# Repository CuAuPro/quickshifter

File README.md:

# Quickshifter
Quickshifter for motorcycle.

<!-- ABOUT THE PROJECT -->
## About The Project

Quickshifter for motorcycles based on measured force on gearbox. Implemented is pull-type quicksihfter but it allows, with small modifications, push-type also.

<p align="right">(<a href="#top">back to top</a>)</p>

### Built With

* [KiCad](https://www.kicad.org/)
* [STM32CubeIDE](https://www.st.com/en/development-tools/stm32cubeide.html)

<p align="right">(<a href="#top">back to top</a>)</p>

### Contents

* PCB
* Firmware

<p align="right">(<a href="#top">back to top</a>)</p>

<!-- CONTACT -->
## Contact

Kristjan Cuznar - [LinkedIn](https://www.linkedin.com/in/kristjan-cuznar/) - kristjancuznar0@gmail.com

Project Link: [https://github.com/CuAuPro/quickshifter)

<p align="right">(<a href="#top">back to top</a>)</p>

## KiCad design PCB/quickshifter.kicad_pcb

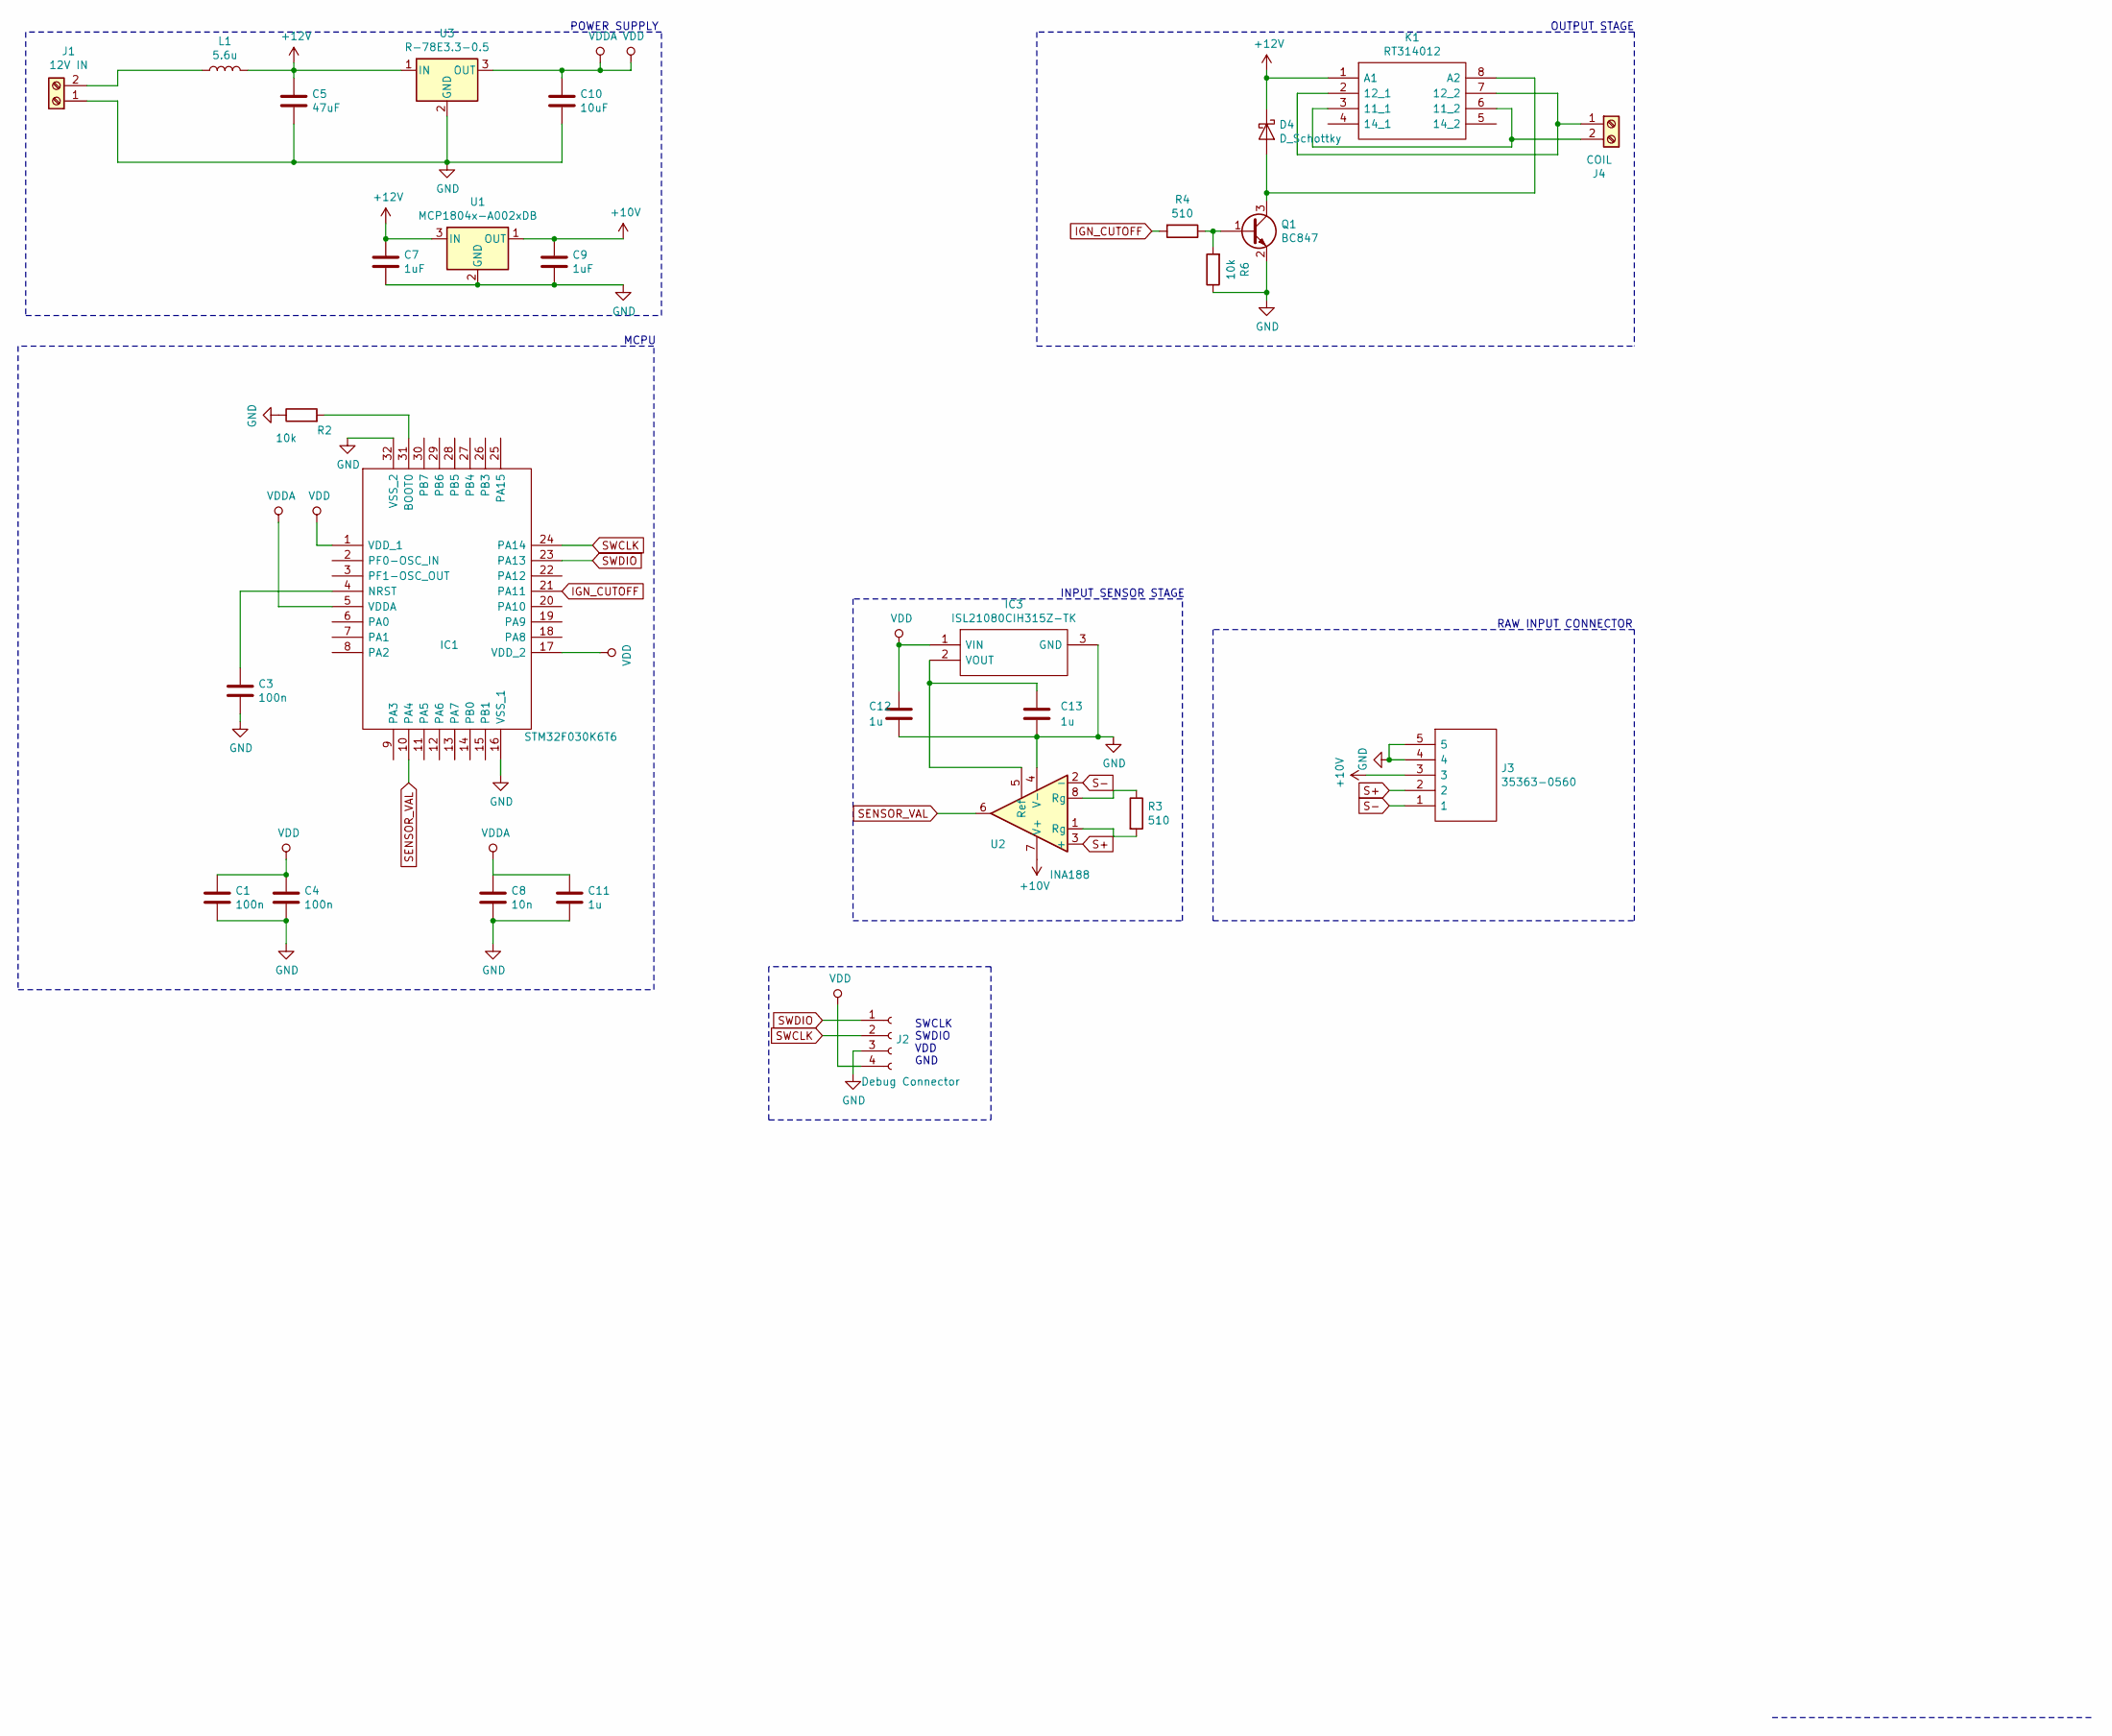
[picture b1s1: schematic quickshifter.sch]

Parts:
C1, C3, C4: 100n; C_0805_2012Metric_Pad1.18x1.45mm_HandSolder
C5: 47uF; C_0805_2012Metric_Pad1.18x1.45mm_HandSolder
C7, C9: 1uF; C_0805_2012Metric_Pad1.18x1.45mm_HandSolder
C8: 10n; C_0805_2012Metric_Pad1.18x1.45mm_HandSolder
C10: 10uF; C_0805_2012Metric_Pad1.18x1.45mm_HandSolder
C11, C12, C13: 1u; C_0805_2012Metric_Pad1.18x1.45mm_HandSolder
D4: D_Schottky; D_SOD-123; Farnell 2473410
IC1: STM32F030K6T6; QFP80P900X900X120-32N; Farnell 2432085
IC3: ISL21080CIH315Z-TK; SOT95P237X112-3N; Farnell 2358142
J1: 12V IN; SHDR2W80P0X350_1X2_840X920X720P
J2: Debug Connector; PinHeader_1x04_P2.54mm_Vertical
J3: 35363-0560; 353630560; Farnell 3107233
J4: COIL; SHDR2W80P0X350_1X2_840X920X720P
K1: RT314012; RT314005_2; Farnell 1629044
L1: 5.6u; L_0805_2012Metric_Pad1.15x1.40mm_HandSolder
Q1: BC847; SOT-23
R2, R6: 10k; R_0805_2012Metric_Pad1.20x1.40mm_HandSolder
R3, R4: 510; R_0805_2012Metric_Pad1.20x1.40mm_HandSolder
U1: MCP1804x-A002xDB; SOT-223-3_TabPin2
U2: INA188; SOIC-8_3.9x4.9mm_P1.27mm
U3: R-78E3.3-0.5; Converter_DCDC_RECOM_R-78E-0.5_THT

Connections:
+10V: C9.1, J3.3, U1.1 (OUT), U2.7 (V+)
+12V: C5.1, C7.1, D4.1 (K), K1.1 (A1), L1.2, U1.3 (IN), U3.1 (IN)
GND: C1.2, C3.2, C4.2, C5.2, C7.2, C8.2, C9.2, C10.2, C11.2, C12.2, C13.2, IC1.16 (VSS_1), IC1.32 (VSS_2), IC3.3 (GND), J1.1, J2.3, J3.4, J3.5, Q1.2 (E), R2.1, R6.1, U1.2 (GND), U2.4 (V-), U3.2 (GND)
IGN_CUTOFF: IC1.21 (PA11), R4.2
unnamed: C3.1, IC1.4 (NRST)
unnamed: C13.1, IC3.2 (VOUT), U2.5 (Ref)
unnamed: D4.2 (A), K1.8 (A2), Q1.3 (C)
unnamed: IC1.31 (BOOT0), R2.2
unnamed: J1.2, L1.1
unnamed: J4.1, K1.2 (12_1), K1.7 (12_2)
unnamed: J4.2, K1.3 (11_1), K1.6 (11_2)
unnamed: Q1.1 (B), R4.1, R6.2
unnamed: R3.1, U2.8 (Rg)
unnamed: R3.2, U2.1 (Rg)
S+: J3.2, U2.3 (+)
S-: J3.1, U2.2 (-)
SENSOR_VAL: IC1.10 (PA4), U2.6
SWCLK: IC1.24 (PA14), J2.2
SWDIO: IC1.23 (PA13), J2.1
VDD: C1.1, C4.1, C8.1, C10.1, C11.1, C12.1, IC1.1 (VDD_1), IC1.5 (VDDA), IC1.17 (VDD_2), IC3.1 (VIN), J2.4, U3.3 (OUT)

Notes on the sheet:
POWER SUPPLY
MCPU
SWCLK SWDIO VDD GND
RAW INPUT CONNECTOR
INPUT SENSOR STAGE
OUTPUT STAGE

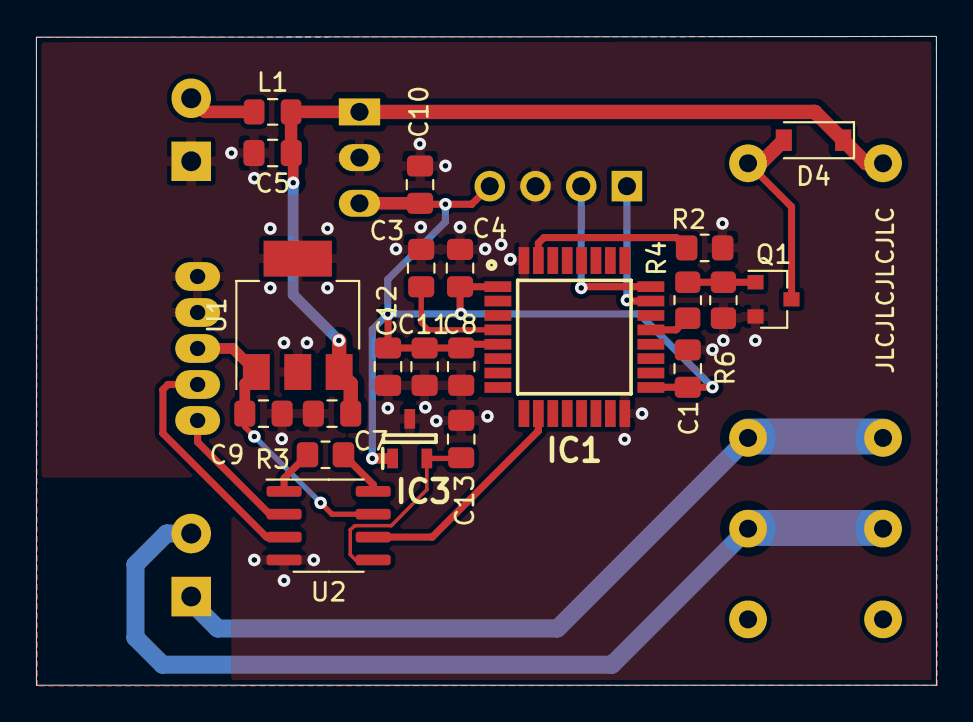
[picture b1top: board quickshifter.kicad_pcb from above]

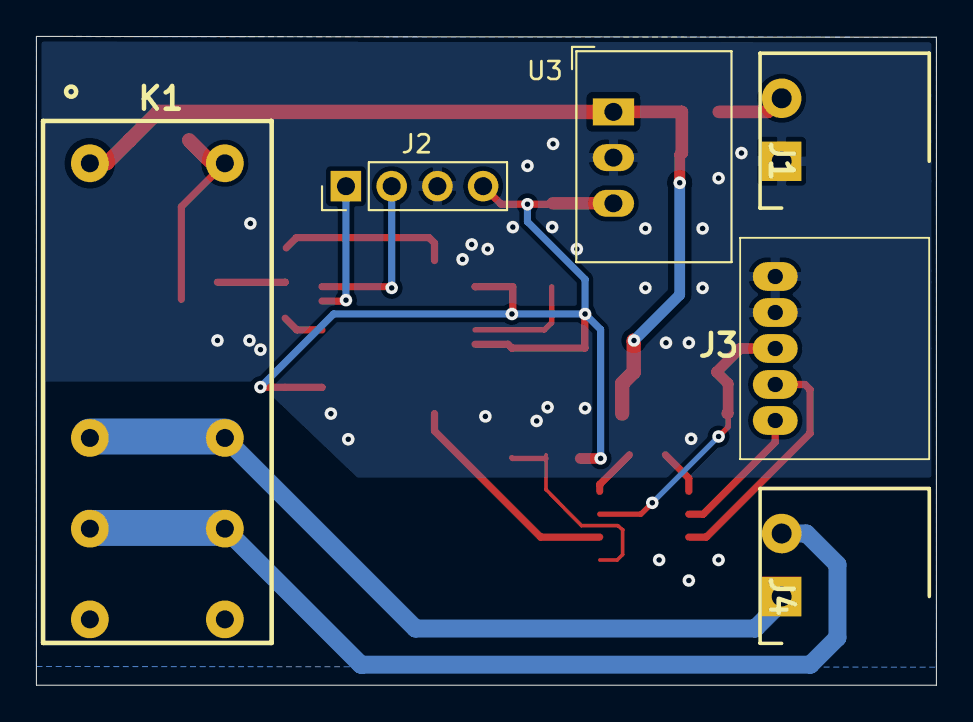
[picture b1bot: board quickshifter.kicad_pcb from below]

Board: 2 copper layers, 50.0 x 36.0 mm, 28 parts (6 on the bottom side), 20 nets.

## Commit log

2022-06-25 Initial commit.
